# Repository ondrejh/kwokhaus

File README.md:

# Kwokhaus

Attempt on some eggish automation.

## Configuring (door)

Door firmware (`fw/src_door`) keeps its configuration in the last flash sector, so it survives firmware updates (only full flash erase wipes it). When no valid config is stored, defaults from `config.h` are used (name `KWOK`, broadcast period 30 min).

Configure over USB serial only (not over the Meshtastic UART), one command per line:

command | answer | description
--- | --- | ---
`CFG?` | `CFG: NAME=KWOK BRPER=1800 CNT=0` | show config (CNT = flash save counter)
`NAME=<name>` | `CFG: NAME=<name>` | device name used in messages, 1-16 chars `A-Z a-z 0-9 _ -`
`BRPER=<s>` | `CFG: BRPER=<s>` | status broadcast period in seconds (10 .. 86400), `0` = no periodic broadcast (status is still sent on change and on `?`)

Invalid value is answered with `CFG: ERR ...`. Changes are applied immediately and saved to flash when the motor is stopped (`CFG: saved (cnt N)`, or `CFG: save skipped (same as stored)`).

### Config tool

Easiest way is `fw/test/door_config.py` (needs `pyserial`, see `fw/test/requirements.txt`). It reads the config, asks whether to change it, asks for the values (Enter keeps current one), shows the changes and writes them after confirmation. Then it waits for the flash save and reads the config back to verify.

```
cd fw/test
./door_config.py                      # default port /dev/ttyACM0
./door_config.py --port /dev/ttyACM1
```

Options: `--port`, `--timeout` (answer timeout, default 2 s), `--save-timeout` (wait for flash save, default 30 s - save waits while motor runs).

Manually (second door example): connect USB, open terminal (e.g. `picocom /dev/ttyACM0`), type `NAME=KMUT`, check with `CFG?`.

Note: when `config_t` layout changes, increase `CONF_VERSION` in `nvdata.h` (and migrate old data in `load_config()`), otherwise the stored config falls back to defaults.

# ToDo

- [ ] remote setting
- [x] non volatile config (not hard coded) - door: name, broadcast period

---

## Kwokhaus

- door motor controll
- remote connection with Meshtastic (encrypted LoRa)
- Home Assistant integration

## Kwakhaus

### Lock

Simple lock controll with serial connection to Meshtastic.

Source directory fw/src_lock

- [x] clear project (remove display and rtc)
- [x] check lock / unlock response
- [x] create unlock trigger (remote only)
- [x] repeat status message every half an hour

- [x] connect meshtastic message to home assistant
- [x] find out how to send messages from home assistant

- [ ] light with dimmer
- [ ] return more info on status (voltage, temperature, ect.)

#### Communication protocol

function | command | answer | example
--- | --- | --- | ---
get status | NAME ? | NAME: LODKED/UNLOCKED | RX: ``KWAK ?```
| | | | TX: ```KWAK: LOCKED/UNLOCKED```
unlock | NAME UNLOCK | | RX: ```KWAK UNLOCK```
| | | |
status change | | NAME LOCKED/UNLOCKED | TX: ```KWAK: LOCKED/UNLOCKED```

#### Building, flashing

From source directory ```fw``` run ```./rebuild_lock.sh```. Reset the board to bootloader by ```./utils/reset.sh```, flash it by ```./utils/flash.sh```.

#### Connecting MQTT to HA

Let there be ```mqtt.yaml``` file in your config. And let there be in you ```configuration.yaml``` file line ```mqtt: !include mqtt.yaml```. Than, somewhere it the file there shoul be:

```
  - name: "MediumFast Last Message"
    unique_id: "mediumfast_last_message"
    state_topic: !secret meshtastic_mediumfast_topic
    value_template: >-
      {% if value_json.payload.text is defined %}
        {{ (value_json.payload.text) }}
      {% else %}
        {{ this.state }}
      {% endif %}
```

Note that, you also need to have secret definition in your secret.yaml file. This is how HA works. Love it or hate it.

From now on, youre having last MediumFast message in sensor.medium_fast_message entity. One can probably imagine how to change this for his own secret channel. Cause the otherone can probably imagine, its not a good idea to have LOCK driver connected to the public channel.

### Key

Dedicated Meshtastic connected device, monitoring Lock status. It has an RGB led to indicate whether lock is locked or unlocked. It also has the button to unlock it remotelly.

#### ToDo

- [x] chatch lock unlock messages, display
- [x] detect button press, send unlock message
- [x] send status request when no status update

##### Technical

- [ ] wifi, mqtt reconnecting
- [ ] mqtt dedicated files (not to plague main)

#### Features

- button
  - to unlock remote lock
- rgb led
  - to indicate remote lock status
- mqtt connection
  - bridge between secret Meshtastic channel and MQTT
  - backup channel for HA, in case main transceiver doesn't work

#### Prototype

---

Obsolette

### Idea (not to forget)

- rubber duck splash screen

### Siple tasks

- [x] trigger by pushbutton (test)
- [ ] trigger on time
- [ ] send status on idle (every 15 minutes)
- [ ] send status on event
- [ ] draw display function chart
- [x] create and test function to store data in flash (or find lib)
  - improve nvdata.c/h
- [x] parse incoming messages
  - [x] reply on ?
  - [x] T to set time
  - [x] Z to set zone
  - [x] U to set unlock time
- [x] simple pushbutton (any bool input) filtering
- [ ] measure trigger charge voltage

### Hardware needed

- [x] rtc module
- [x] display
- [x] communication port (uart)
- [ ] charge pump
  - to charge trigger from lower voltage (single lipo)

### Functionality and features

- [x] filter incoming messages
- [x] show time
- [x] set time
- [x] set trigger time
- [ ] set time, trigger and zone localy (button, display)
- [ ] trigger on time
- [ ] showing status on display (unlocked, locked, next unlock in ..)
- [x] remote addministration by com. port

### Communication protocol (so far)

function | command | answer | example
--- | --- | --- | ---
get status | NAME ? | NAME LODKED/UNLOCKED Uhh:mm Thh:mm(z) | RX: ```KWAK ?```
| | | | TX: ```KWAK: LOCKED U11:03 T10:08(+2)```
set local time | NAME Thh:mm | NAME: Thh:mm | RX: ```KWAK T12:00```
| | | | TX: ```KWAK: T12:00```
set unlock time (local) | NAME Uhh:mm | NAME: Uhh:mm | RX: ```KWAK U12:01```
| | | | TX: ```KWAK: U12:01```
set zone | NAME Z+/-z | NAME: Z+/-z | RX: ```KWAK Z+1```
| | | | TX: ```KWAK: Z+1```

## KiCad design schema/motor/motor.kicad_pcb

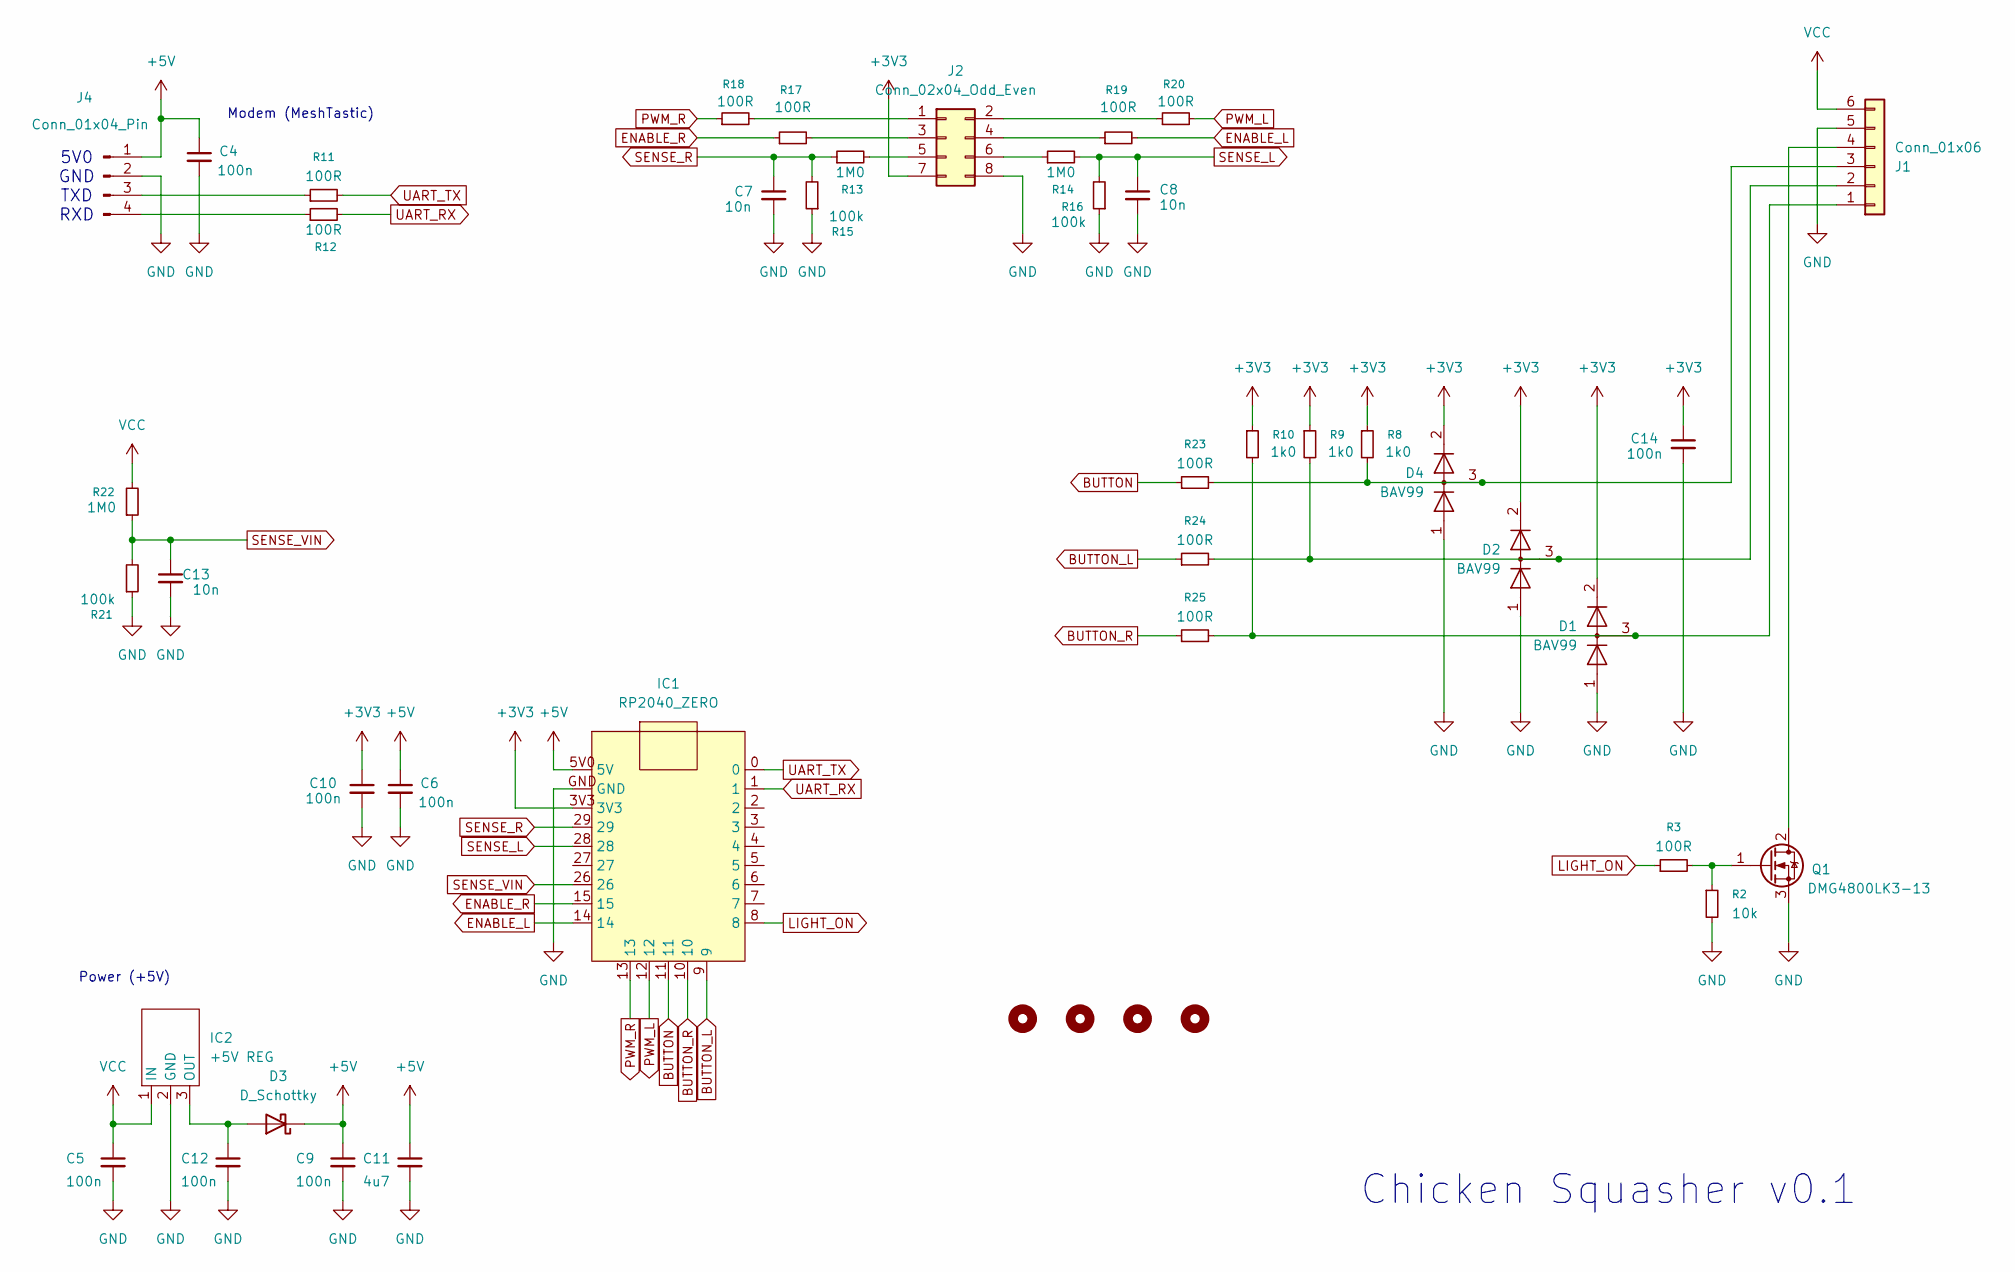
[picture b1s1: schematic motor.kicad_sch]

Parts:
C4, C5, C6, C9, C10, C12, C14: 100n; C_0603_1608Metric
C7, C8, C13: 10n; C_0603_1608Metric
C11: 4u7; C_1206_3216Metric
D1, D2, D4: BAV99; SOT-23
D3: D_Schottky; D_SOD-123F
H1, H2, H3, H4: MountingHole; MountingHole_3.2mm_M3
IC1: RP2040_ZERO
IC2: +5V REG; Untitled_3
J1: Conn_01x06; TerminalBlock_Phoenix_MKDS-1,5-6-5.08_1x06_P5.08mm_Horizont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
J2: Conn_02x04_Odd_Even; PinSocket_2x04_P2.54mm_Vertical
J4: Conn_01x04_Pin; Solder_Terminal_4p
Q1: DMG4800LK3-13; TO-252-3_TabPin2
R2: 10k; R_0603_1608Metric
R3, R11, R12, R17, R18, R19, R20, R23, R24, R25: 100R; R_0603_1608Metric
R8, R9, R10: 1k0; R_0603_1608Metric
R13, R14, R22: 1M0; R_0603_1608Metric
R15, R16, R21: 100k; R_0603_1608Metric

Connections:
+3V3: C10.1, C14.1, D1.2 (A), D2.2 (A), D4.2 (A), IC1.3V3, J2.7, R8.1, R9.1, R10.1
+5V: C4.1, C6.1, C9.1, C11.1, D3.1 (K), IC1.5V0 (5V), J4.1
BUTTON: IC1.11, R23.1
BUTTON_L: IC1.9, R24.1
BUTTON_R: IC1.10, R25.1
ENABLE_L: IC1.14, R19.2
ENABLE_R: IC1.15, R17.1
GND: C4.2, C5.2, C6.2, C7.2, C8.2, C9.2, C10.2, C11.2, C12.2, C13.2, C14.2, D1.1 (K), D2.1 (K), D4.1 (K), IC1.GND, IC2.2 (GND), J1.5, J2.8, J4.2, Q1.3 (S), R2.2, R15.1, R16.1, R21.1
LIGHT_ON: IC1.8, R3.1
unnamed: C12.1, D3.2 (A), IC2.3 (OUT)
unnamed: D1.3 (K), J1.1, R10.2, R25.2
unnamed: D2.3 (K), J1.2, R9.2, R24.2
unnamed: D4.3 (K), J1.3, R8.2, R23.2
unnamed: J1.4, Q1.2 (D)
unnamed: J2.1, R18.2
unnamed: J2.2, R20.1
unnamed: J2.3, R17.2
unnamed: J2.4, R19.1
unnamed: J2.5, R13.2
unnamed: J2.6, R14.1
unnamed: J4.3, R11.1
unnamed: J4.4, R12.1
unnamed: Q1.1 (G), R2.1, R3.2
PWM_L: IC1.12, R20.2
PWM_R: IC1.13, R18.1
SENSE_L: C8.1, IC1.28, R14.2, R16.2
SENSE_R: C7.1, IC1.29, R13.1, R15.2
SENSE_VIN: C13.1, IC1.26, R21.2, R22.1
UART_RX: IC1.1, R12.2
UART_TX: IC1.0, R11.2
VCC: C5.1, IC2.1 (IN), J1.6, R22.2

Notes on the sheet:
Power (+5V)
Chicken Squasher v0.1
Modem (MeshTastic)
5V0 GND TXD RXD

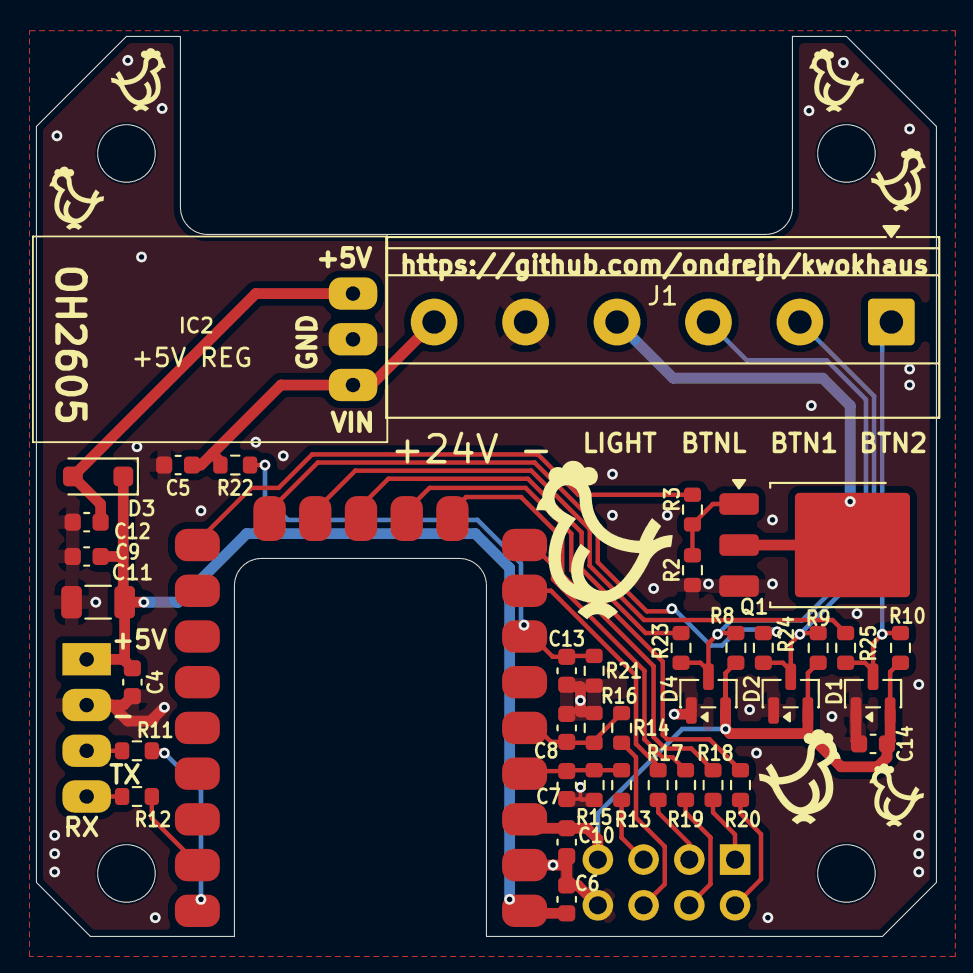
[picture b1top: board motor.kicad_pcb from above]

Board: 2 copper layers, 50.0 x 50.0 mm, 45 parts (1 on the bottom side), 31 nets.

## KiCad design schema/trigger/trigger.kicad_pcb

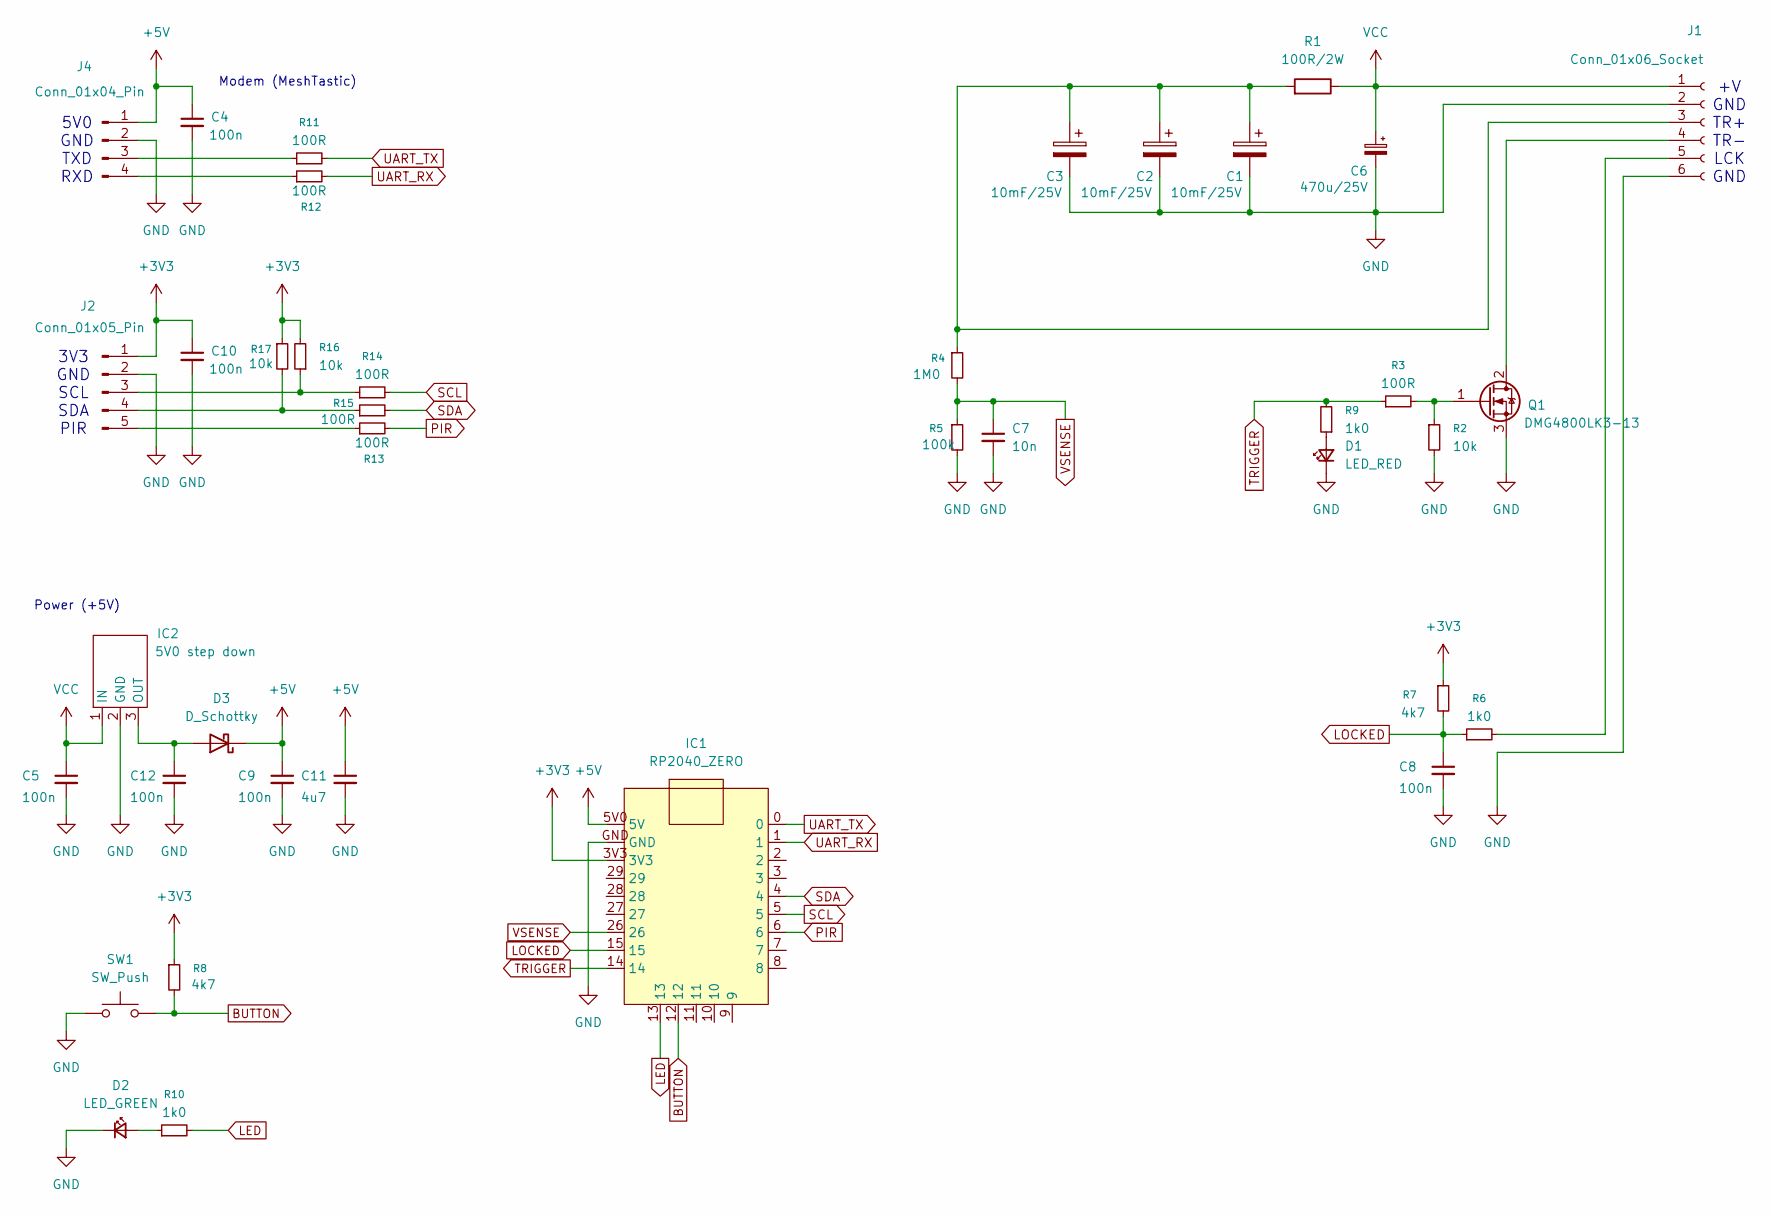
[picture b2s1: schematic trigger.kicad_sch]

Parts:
C1, C2, C3: 10mF/25V; C_36x18
C4, C5, C8, C9, C10, C12: 100n; C_0603_1608Metric
C6: 470u/25V; CP_Radial_D8.0mm_P3.50mm
C7: 10n; C_0603_1608Metric
C11: 4u7; C_1206_3216Metric
D1: LED_RED; LED_0805_2012Metric
D2: LED_GREEN; LED_0805_2012Metric
D3: D_Schottky; D_SOD-123F
IC1: RP2040_ZERO
IC2: 5V0 step down; Untitled_3
J1: Conn_01x06_Socket; Solder_Terminal_6p
J2: Conn_01x05_Pin; Solder_Terminal_5p
J4: Conn_01x04_Pin; Solder_Terminal_4p
Q1: DMG4800LK3-13; TO-252-3_TabPin2
R1: 100R/2W; R_Axial_DIN0414_L11.9mm_D4.5mm_P15.24mm_Horizontal
R2, R16, R17: 10k; R_0603_1608Metric
R3, R11, R12, R13, R14, R15: 100R; R_0603_1608Metric
R4: 1M0; R_0603_1608Metric
R5: 100k; R_0603_1608Metric
R6, R9, R10: 1k0; R_0603_1608Metric
R7, R8: 4k7; R_0603_1608Metric
SW1: SW_Push; SW_SPST_SKQG_WithStem

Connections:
+3V3: C10.1, IC1.3V3, J2.1, R7.1, R8.1, R16.2, R17.1
+5V: C4.1, C9.1, C11.1, D3.1 (K), IC1.5V0 (5V), J4.1
BUTTON: IC1.12, R8.2, SW1.2
GND: C1.2, C2.2, C3.2, C4.2, C5.2, C6.2, C7.2, C8.2, C9.2, C10.2, C11.2, C12.2, D1.1 (K), D2.1 (K), IC1.GND, IC2.2 (GND), J1.2, J1.6, J2.2, J4.2, Q1.3 (S), R2.2, R5.2, SW1.1
LED: IC1.13, R10.2
LOCKED: C8.1, IC1.15, R6.1, R7.2
unnamed: D1.2 (A), R9.1
unnamed: D2.2 (A), R10.1
unnamed: C12.1, D3.2 (A), IC2.3 (OUT)
unnamed: C1.1, C2.1, C3.1, J1.3, R1.2, R4.1
unnamed: J1.4, Q1.2 (D)
unnamed: J1.5, R6.2
unnamed: J2.3, R14.1, R16.1
unnamed: J2.4, R15.1, R17.2
unnamed: J2.5, R13.1
unnamed: J4.3, R11.1
unnamed: J4.4, R12.1
unnamed: Q1.1 (G), R2.1, R3.2
PIR: IC1.6, R13.2
SCL: IC1.5, R14.2
SDA: IC1.4, R15.2
TRIGGER: IC1.14, R3.1, R9.2
UART_RX: IC1.1, R12.2
UART_TX: IC1.0, R11.2
VCC: C5.1, C6.1, IC2.1 (IN), J1.1, R1.1
VSENSE: C7.1, IC1.26, R4.2, R5.1

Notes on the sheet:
+V GND TR+ TR- LCK GND
3V3 GND SCL SDA PIR
Power (+5V)
Modem (MeshTastic)
5V0 GND TXD RXD

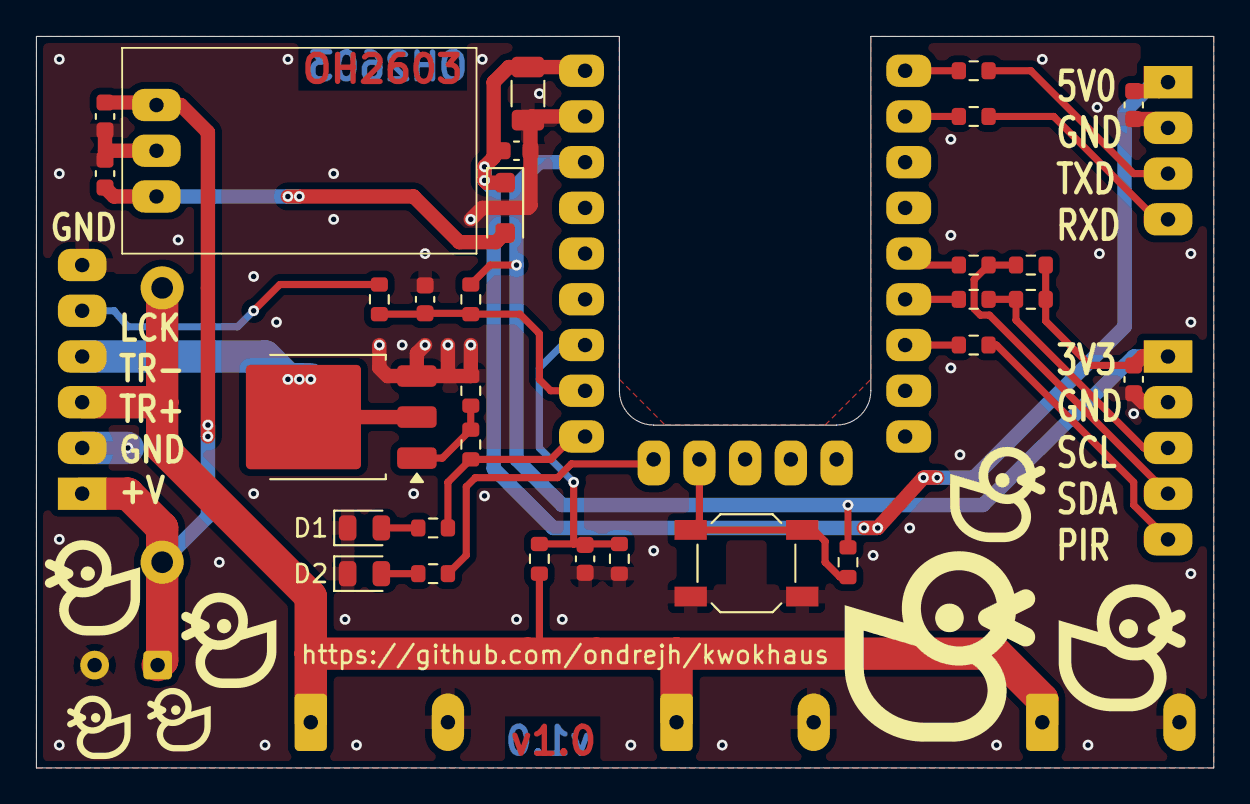
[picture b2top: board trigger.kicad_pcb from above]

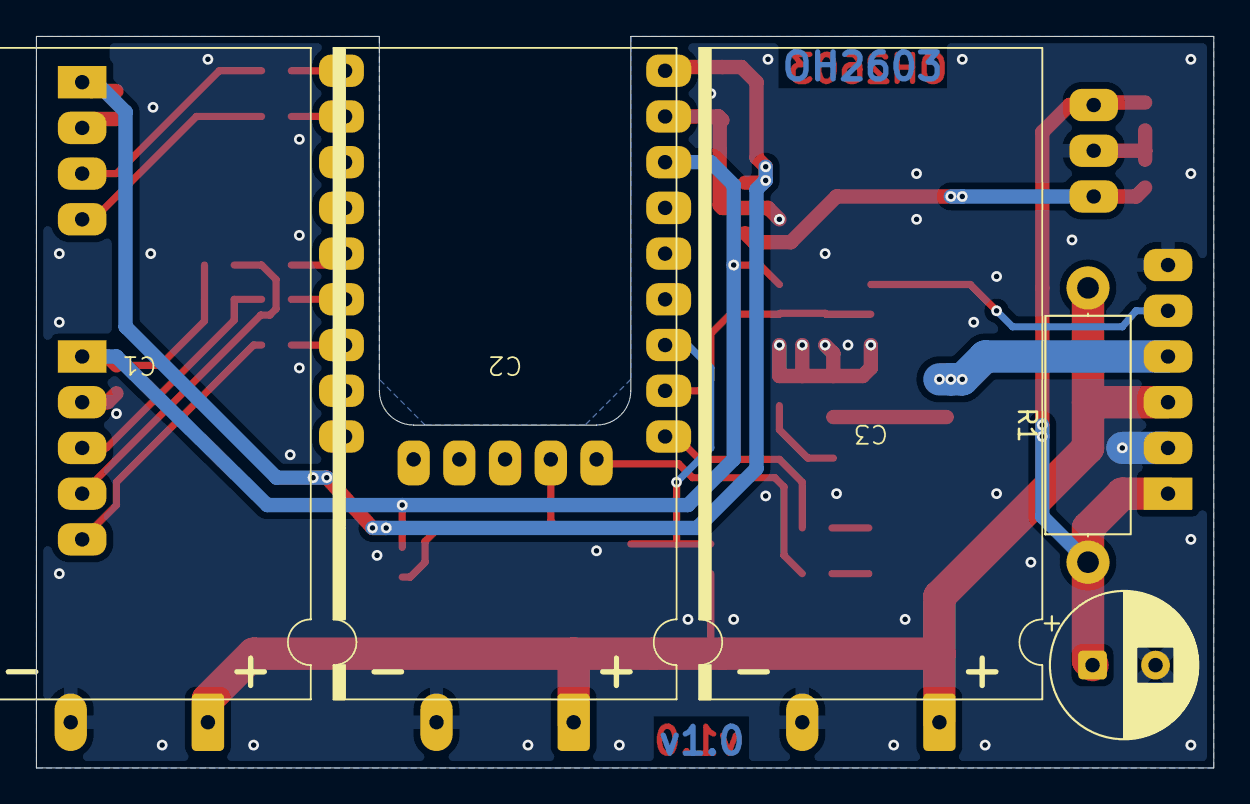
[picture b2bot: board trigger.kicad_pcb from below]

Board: 2 copper layers, 65.4 x 40.6 mm, 39 parts (5 on the bottom side), 26 nets.

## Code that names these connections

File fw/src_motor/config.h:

#ifndef __CONFIG_H__
#define __CONFIG_H__

// Name will be used as comm identifier
// ToDo: move those into nvram section, create some configuration
// Note: This way I have to build FW for the same HW twice, with
// different comm id. I can imagine config system using USB/UART,
// store data into the section not affected by FW.

#define DEV_NAME "KWOK"
//#define DEV_NAME "KMUT" // second door for (meat) broiler chicken
//#define DEV_NAME "TEST"
//#define DEBUG

// Status timing
#define STATUS_REPEAT_PERIOD 30 * 60 * 1000
#define STATUS_CHANGE_TIMEOUT 32 * 1000

// GPIO
//#define FIRST_PROTOTYPE
#ifdef FIRST_PROTOTYPE

// pin configuration of first prototype
#warning "First prototype pin configuration"

#define BUTTON_LIGHT_PIN 11
#define BUTTON_L_PIN 14
#define BUTTON_R_PIN 15

#define ENABLE_R_PIN 8
#define ENABLE_L_PIN 7
#define PWM_R_PIN 6
#define PWM_L_PIN 5

#define LIGHT_PIN 12

#else // ifdef FIRST_PROTOTYPE

#define BUTTON_L_PIN 9
#define BUTTON_R_PIN 10
#define BUTTON_LIGHT_PIN 11

#define ENABLE_R_PIN 15
#define ENABLE_L_PIN 14
#define PWM_R_PIN 13
#define PWM_L_PIN 12

#define LIGHT_PIN 8

#endif // else FIRST_PROTOTYPE

#define RGB_LED_PIN 16

#define SENSE_R_PIN 29
#define SENSE_R_ADC 3
#define SENSE_L_PIN 28
#define SENSE_L_ADC 2

#define SENSE_VIN_PIN 26
#define SENSE_VIN_ADC 0

#define ADC_POLL_PERIOD 2
#define ADC_OVERSAMPLE 8

#define PWM_PERIOD 62500 // 5kHz
#define VOLT_FULL_PWR 13000 // mV

#define MOTOR_GO_UP (1<<0)
#define MOTOR_GO_DOWN (1<<1)
#define MOTOR_RUNNING (MOTOR_GO_UP | MOTOR_GO_DOWN | MOTOR_FORCE_UP | MOTOR_FORCE_DOWN)
#define MOTOR_IS_UP (1<<2)
#define MOTOR_IS_DOWN (1<<3)
#define MOTOR_IS_END (MOTOR_IS_UP | MOTOR_IS_DOWN)
#define MOTOR_FORCE_UP (1<<4)
#define MOTOR_FORCE_DOWN (1<<5)
#define MOTOR_FORCE (MOTOR_FORCE_UP | MOTOR_FORCE_DOWN)

#define MOTOR_SAFETY_TIMEOUT 30000 // ms (stop motor if it runs for too long without reaching end position)
#define MOTOR_CURRENT_TIMEOUT 400 // ms (stop motor if it runs without current - end switch is reached
#define MOTOR_CURRENT_OFFSET_TIMEOUT 100 // ms (calibrate current offset after motor start)
#define CURRENT1_MIN 0x150 // ADC value (current threshold for motor 1)
#define CURRENT2_MIN 0x040 // ADC value (current threshold for motor 2)

#define LIGHT_DIMMING 10
#define LIGHT_DIMMING_BTN 1000

#define LIGHT_AUTO_OFF 120000 // 2 min
#define LIGHT_DOOR_AUTO_OFF 60 * 5 * 1000 // 5 min

#endif // __CONFIG_H__

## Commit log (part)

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2025-09-26 lock trigger schematic
2025-09-26 not even backbone, just a trial
2025-09-26 led to blink, otherwise it'll never work
2025-09-26 compiles but not working either
2025-09-28 pico examples submodule
2025-09-28 blink
2025-09-28 next steps
2025-09-28 non specified schematic changes (led, maybe?)
2025-09-29 display library
2025-09-29 no sleep
2025-09-29 cleanup
2025-09-30 simple trigger on pushbutton
2025-09-30 readme update
2025-10-02 I2C port scanning
2025-10-02 some utils
2025-10-02 no u8g2, sorry
2025-10-02 get rid of u8g2 submodule .. useless for me
2025-10-02 display and rtc module
2025-10-02 hello world text
2025-10-02 rtc module read/write function (and test)
2025-10-07 button .. will be, one day, maybe
2025-10-07 test button states
2025-10-07 improved model
2025-10-08 font, first trial, no succ..
2025-10-08 Adafruit fonts, thank you
2025-10-08 testing fonts
2025-10-08 display test functions
2025-10-10 models
2025-10-15 show clock
2025-10-16 display size testing
2025-10-16 events moved to extra file
2025-10-16 opening spring holder
2025-10-16 swapped lock logic
2025-10-16 saving mech project
2025-10-16 schematic - uart connection (radio)
2025-10-17 new models
2025-10-17 comm module - echo
2025-10-17 trying to make uart tx on interrupt
2025-10-18 uart comm with buffers
2025-10-18 spacer, because of space
2025-10-23 this is where flash storage functions will go
2025-10-23 some meshtastic parsing and reply
2025-10-26 config load/save functions - need test
2025-10-27 flash sector already defined in sdk
2025-10-27 move time event resolver to events
2025-10-27 set time, set unlock, set zone
2025-10-27 readme update, whats done, new goals, comm protocol
2025-10-28 debug - zone settings, leave cycle on data save
2025-10-30 some new packages
2025-10-31 yet another oled footprint
2025-12-18 motor driver firmware
2026-01-04 vypocet
2026-02-27 simple lock
2026-02-28 baptism of fire
2026-03-04 mqtt example / can compile
2026-03-05 now it works (mqtt)
2026-03-05 comm, quite probably, prepared
2026-03-07 mqtt - serial - meshatastic bridge
2026-03-07 lock status chatching, requesting
2026-03-07 KwakKey functional prototype
2026-03-07 smaller pic
2026-03-07 debug: now i know why it's not resending status
2026-03-15 pcb design
2026-03-21 motor status unknown
2026-03-21 door geometry calculation
2026-03-21 pwm limit in case of overvoltage
2026-03-28 measure voltage, get pwm (not used yet)
2026-03-28 pwm output to save lock coil
2026-03-29 wifi and mqtt reconnecting
2026-03-29 wifi status led blinking (not tested)
2026-04-11 Reconnection debugged (it hasn't ever connected at all)
2026-04-11 Merge, cos I did it twice
2026-04-11 removing some unsused code
2026-04-11 ignore list update
2026-04-11 lock connector cover
2026-04-14 push start, timeout, current stop
2026-04-14 improved status blinking
2026-04-17 bom and some finetuning while first assembly
2026-04-17 some nessesary changes on first assembly
2026-04-17 docs and cleaning
2026-04-17 motor driver schematic .. not even started
2026-04-17 some models
2026-04-20 building motor pcb
2026-04-29 kwokhaus remote controll, fist, fast, ugly
2026-05-13 motor driver layout nearly done
2026-05-13 artkwork
2026-05-15 pravdepodobne starsi verze
2026-05-15 layout done, silk screen needed
2026-05-15 silkscreen (partof)
2026-05-15 silkscreen almost done
2026-05-15 chicken picture missing, only
2026-05-15 now its perfect (silkscreen)
2026-05-16 chicken squasher hw v1.0 - final touch, fabrication
2026-05-16 comment
2026-05-16 todo list for kwak sensor and light features
2026-05-16 pir input and events
2026-05-20 rgb led driver
2026-05-20 light command, timeout
2026-05-20 bme280 basic reading(driver)
2026-05-20 bme280 driver
2026-06-05 kwakhaus light and sensor bodies
2026-06-05 test script for kwakhaus lock remote commands
2026-06-06 environment to status message
2026-06-06 callable script
2026-06-06 lock fw todo list
